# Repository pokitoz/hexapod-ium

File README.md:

# hexapod-ium

An hexapod robot using arduino and servo motors.
Manufacturing (PCB, 3D prints) and component assembly (PCBA) were done with PCBWay: https://www.pcbway.com/.

## Hardware

See the Kicad project in hw/ folder.

There is a Kicad Pluggin (https://www.pcbway.com/blog/News/PCBWay_Plug_In_for_KiCad_3ea6219c.html)
, 
simplifying the order process with PCBWay as the Gerber and BOM are filled in.

The design is reviewed and manufactured rapidely; which was very useful for this project.

### PCB

Kicad was used for the PCB design to add 2xPCA9865 and an ESP32.

### 3D Parts 

3D Printed parts can be done using a Prusa or Bamboo or any other 3d printer like the first iteration. 
But it was simpler to use PCBWay and the quality was better than printing on my own. The parameter used were:
- Resin Standard white material (UTR 8360)
- SLA

Design check and delivery was fast.

### Components

- 6x Leg (3 of them must be mirrored)
- 6x Holder
- 12 servo motors: MG90S or SG90 Micro Servo with screws
- 1 Arduino Uno
- PCA9865 (https://learn.adafruit.com/16-channel-pwm-servo-driver?view=all)
- Blu-tack
- Jumper cables

Need 5V for the motors board. VCC will be propagated to the main board (Arduino, ESP32,..)

You will need at least 2A upper limit to move all the motors at once.

## Software

### Arduino

Basic Arduino program to activate all the servo.
See the pinout in the .ino file. The VCC going out of the PCA9868 should go to the 5V of the board.

### ESP32

Might need driver https://www.silabs.com/developer-tools/usb-to-uart-bridge-vcp-drivers?tab=downloads

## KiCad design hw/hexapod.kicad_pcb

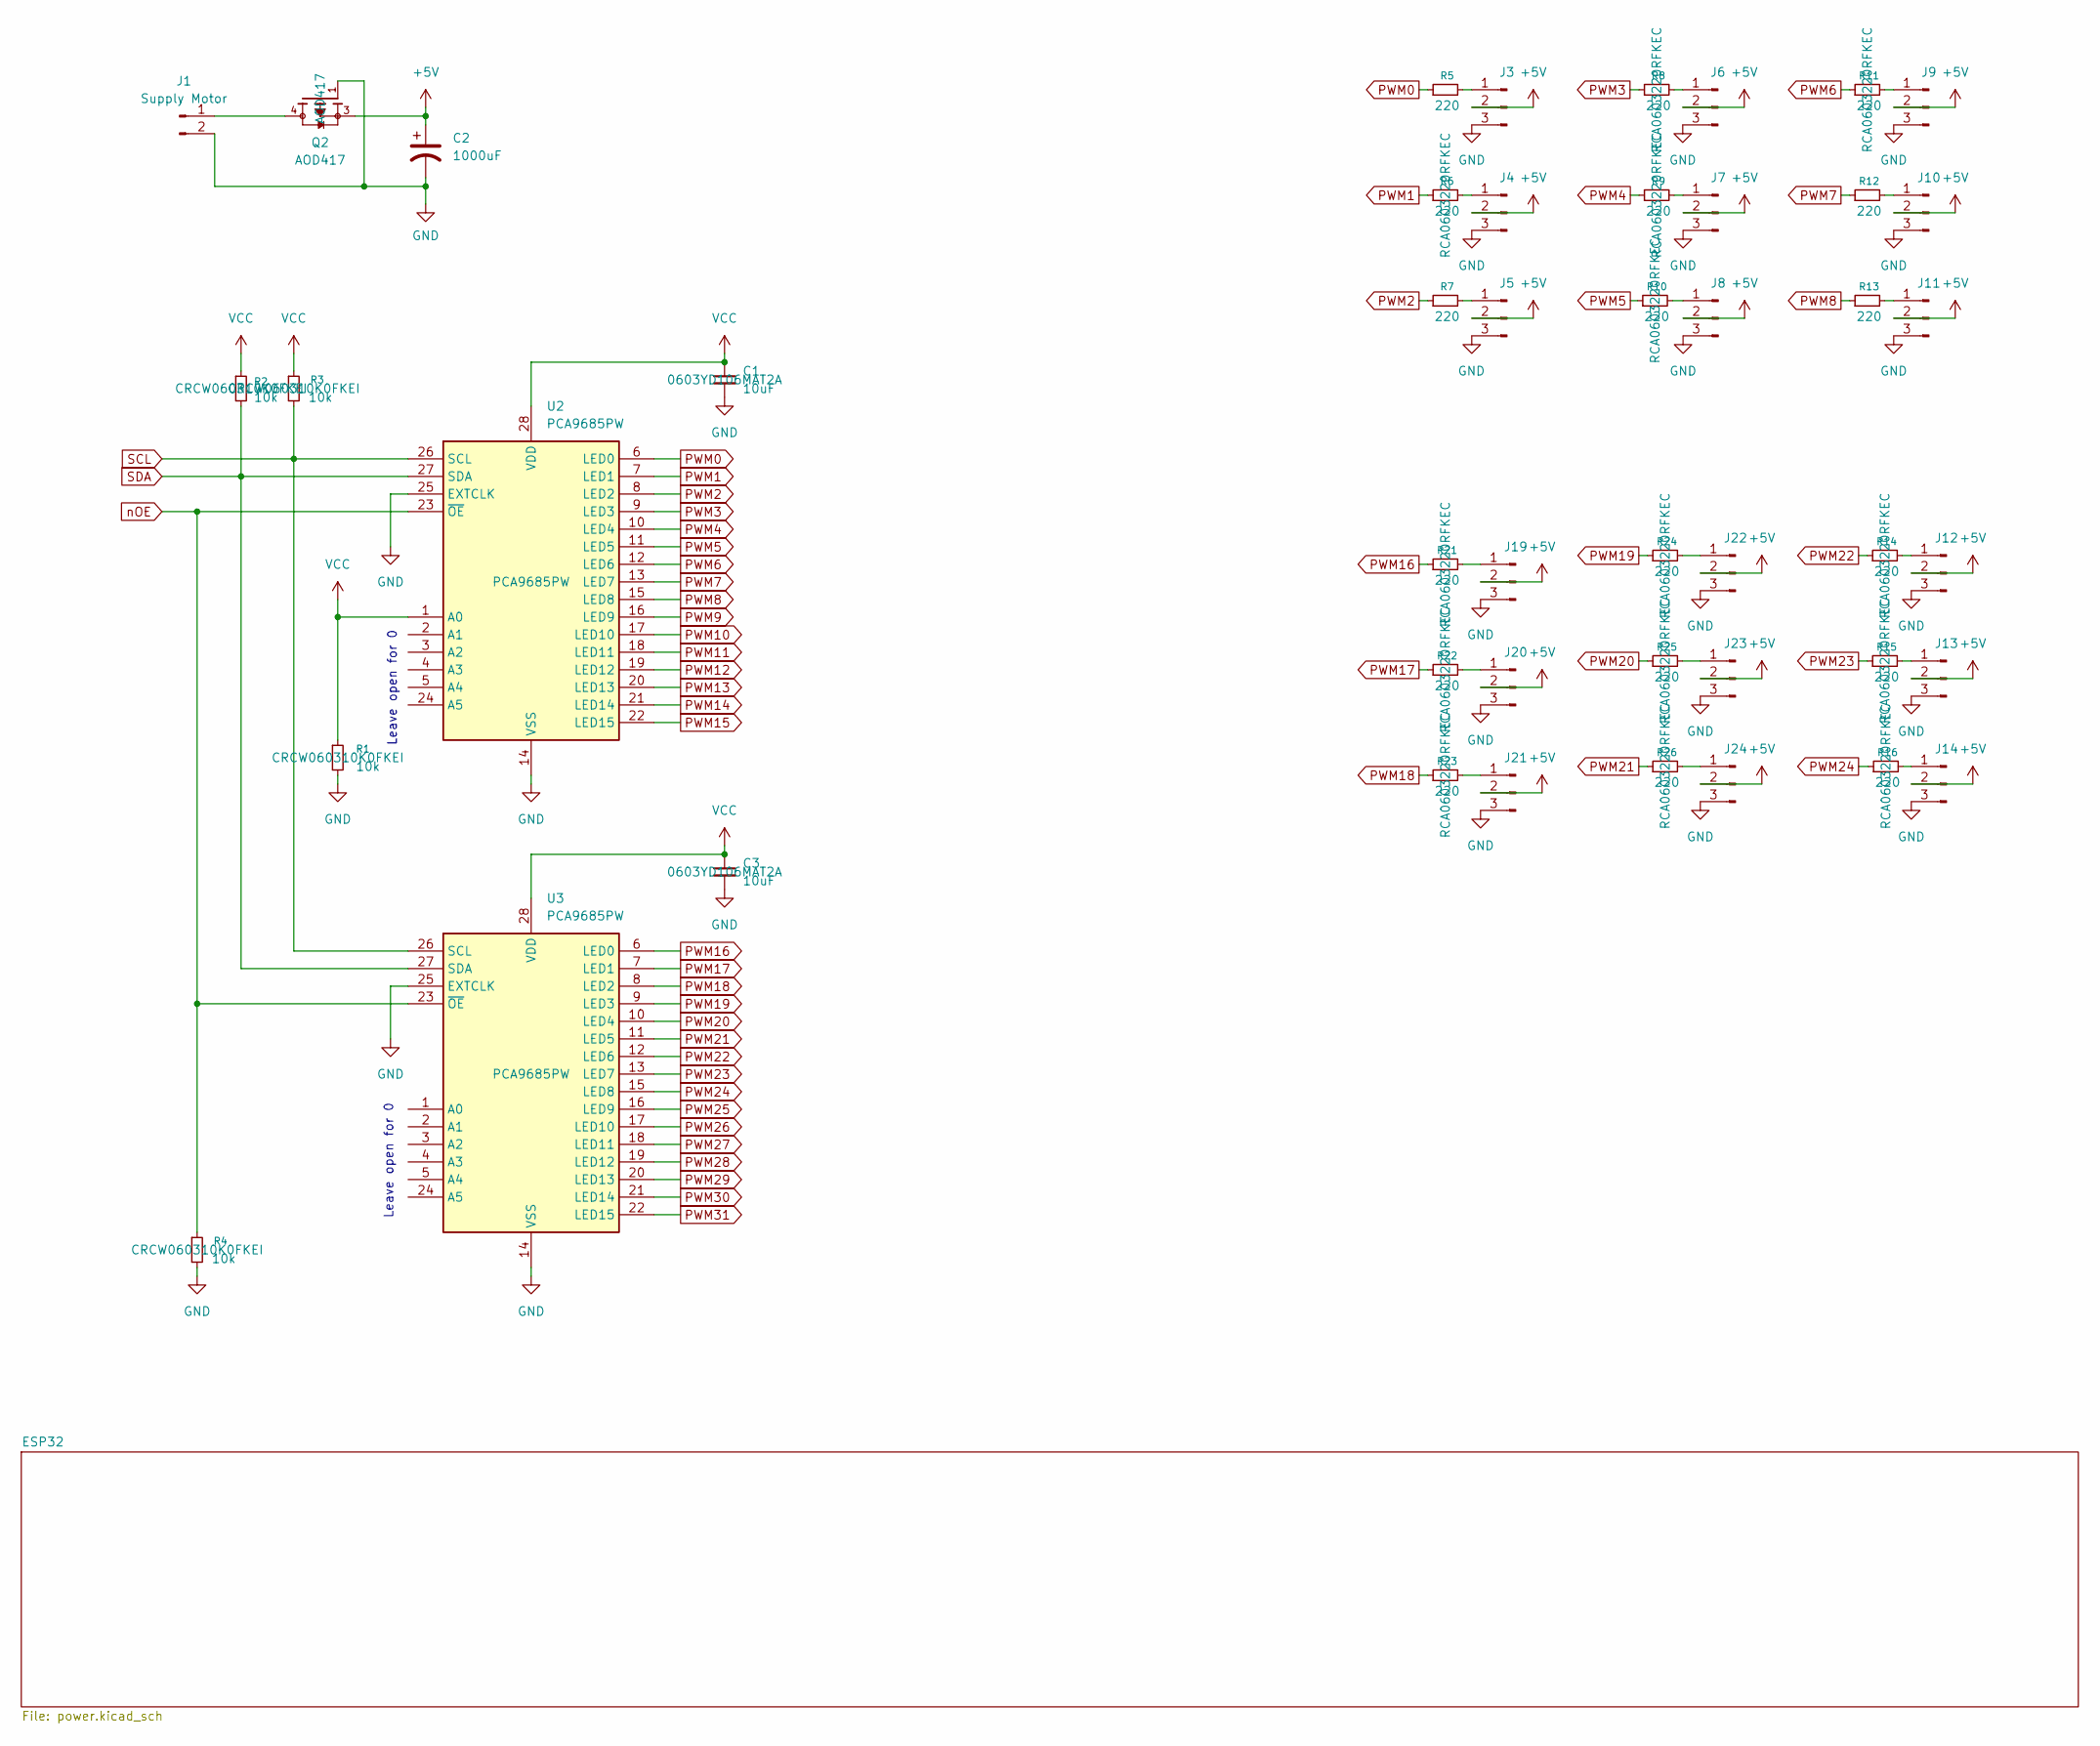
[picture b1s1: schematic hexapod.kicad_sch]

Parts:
C1, C3: 10uF; C_0603_1608Metric; Part 0603YD106MAT2A
C2: 1000uF; CAPPRD500W60D1000H1350
J1: Supply Motor; AMASS_XT30U-M_1x02_P5.0mm_Vertical
J3, J4, J5, J6, J7, J8, J9, J10, J11, J12, J13, J14, J19, J20, J21, J22, J23, J24: Conn_01x03_Pin; PinHeader_1x03_P2.54mm_Vertical
Q2: AOD417; DPAK228P994X240_3N; PARTREV U
R1, R2, R3, R4: 10k; R_0603_1608Metric_Pad0.98x0.95mm_HandSolder; Part CRCW060310K0FKEI
R5, R6, R7, R8, R9, R10, R11, R12, R13, R14, R15, R16, R21, R22, R23, R24, R25, R26: 220; R_0603_1608Metric_Pad0.98x0.95mm_HandSolder; Part RCA0603220RFKEC
U2, U3: PCA9685PW; TSSOP-28_4.4x9.7mm_P0.65mm; Part PCA9685PW

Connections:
+5V: C2.1, J3.2, J4.2, J5.2, J6.2, J7.2, J8.2, J9.2, J10.2, J11.2, J12.2, J13.2, J14.2, J19.2, J20.2, J21.2, J22.2, J23.2, J24.2, Q2.3
GND: C1.2, C2.2, C3.2, J1.2, J3.3, J4.3, J5.3, J6.3, J7.3, J8.3, J9.3, J10.3, J11.3, J12.3, J13.3, J14.3, J19.3, J20.3, J21.3, J22.3, J23.3, J24.3, Q2.1, R1.2, R4.2, U2.14 (VSS), U2.25 (EXTCLK), U3.14 (VSS), U3.25 (EXTCLK); also elsewhere on the board
unnamed: J1.1, Q2.4
unnamed: J3.1, R5.2
unnamed: J4.1, R6.2
unnamed: J5.1, R7.2
unnamed: J6.1, R8.2
unnamed: J7.1, R9.2
unnamed: J8.1, R10.2
unnamed: J9.1, R11.2
unnamed: J10.1, R12.2
unnamed: J11.1, R13.2
unnamed: J12.1, R14.2
unnamed: J13.1, R15.2
unnamed: J14.1, R16.2
unnamed: J19.1, R21.2
unnamed: J20.1, R22.2
unnamed: J21.1, R23.2
unnamed: J22.1, R24.2
unnamed: J23.1, R25.2
unnamed: J24.1, R26.2
PWM0: R5.1, U2.6 (LED0)
PWM1: R6.1, U2.7 (LED1)
PWM2: R7.1, U2.8 (LED2)
PWM3: R8.1, U2.9 (LED3)
PWM4: R9.1, U2.10 (LED4)
PWM5: R10.1, U2.11 (LED5)
PWM6: R11.1, U2.12 (LED6)
PWM7: R12.1, U2.13 (LED7)
PWM8: R13.1, U2.15 (LED8)
PWM9: U2.16 (LED9)
PWM10: U2.17 (LED10)
PWM11: U2.18 (LED11)
PWM12: U2.19 (LED12)
PWM13: U2.20 (LED13)
PWM14: U2.21 (LED14)
PWM15: U2.22 (LED15)
PWM16: R21.1, U3.6 (LED0)
PWM17: R22.1, U3.7 (LED1)
PWM18: R23.1, U3.8 (LED2)
PWM19: R24.1, U3.9 (LED3)
PWM20: R25.1, U3.10 (LED4)
PWM21: R26.1, U3.11 (LED5)
PWM22: R14.1, U3.12 (LED6)
PWM23: R15.1, U3.13 (LED7)
PWM24: R16.1, U3.15 (LED8)
PWM25: U3.16 (LED9)
PWM26: U3.17 (LED10)
PWM27: U3.18 (LED11)
PWM28: U3.19 (LED12)
PWM29: U3.20 (LED13)
PWM30: U3.21 (LED14)
PWM31: U3.22 (LED15)
SCL: R3.2, U2.26 (SCL), U3.26 (SCL); also elsewhere on the board
SDA: R2.2, U2.27 (SDA), U3.27 (SDA); also elsewhere on the board
VCC: C1.1, C3.1, R1.1, R2.1, R3.1, U2.1 (A0), U2.28 (VDD), U3.28 (VDD); also elsewhere on the board
nOE: R4.1, U2.23 (~OE), U3.23 (~OE)

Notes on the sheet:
Leave open for 0

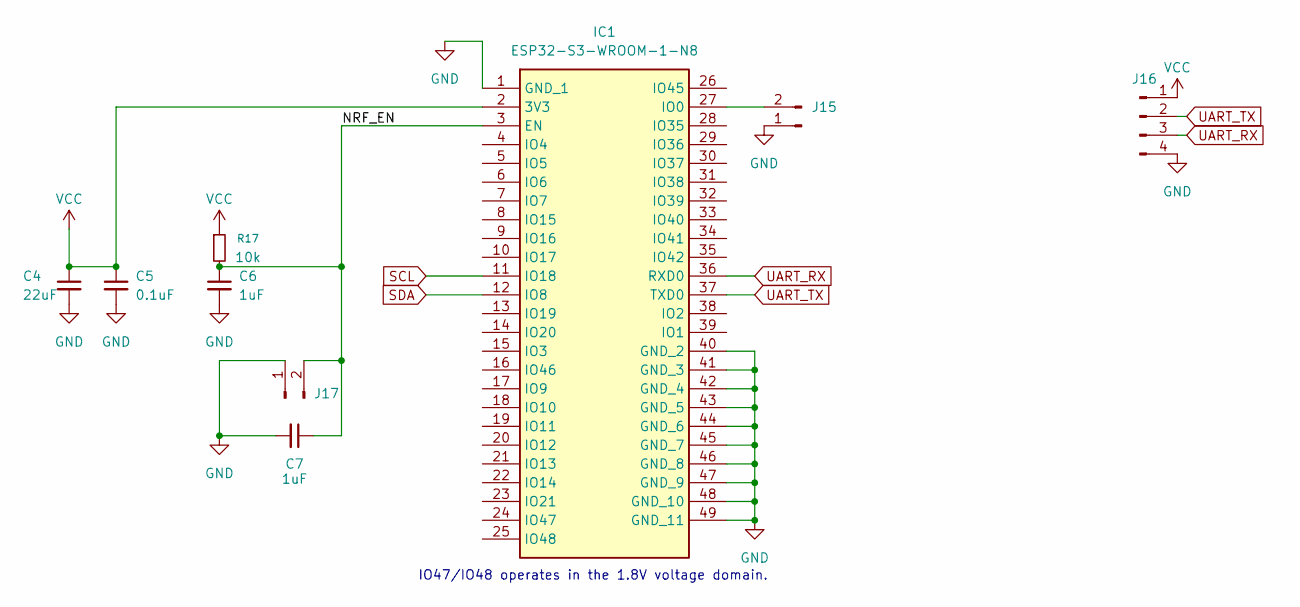
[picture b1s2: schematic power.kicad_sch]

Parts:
C4: 22uF; C_0603_1608Metric; Part 0603YD106MAT2A
C5: 0.1uF; C_0603_1608Metric; Part 0603YD106MAT2A
C6, C7: 1uF; C_0603_1608Metric; Part 0603YD106MAT2A
IC1: ESP32-S3-WROOM-1-N8; ESP32S3WROOM1N8R2; Mouser Part Number 356-ESP32-S3WROOM1N8
J15, J17: Conn_01x02_Pin; PinHeader_1x02_P2.54mm_Vertical
J16: Conn_01x04_Pin; PinHeader_1x04_P2.54mm_Vertical
R17: 10k; R_0603_1608Metric_Pad0.98x0.95mm_HandSolder; Part CRCW060310K0FKEI

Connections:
/ESP32/NRF_EN: C6.1, C7.1, IC1.3 (EN), J17.2, R17.2
GND: C4.2, C5.2, C6.2, C7.2, IC1.1 (GND_1), IC1.40 (GND_2), IC1.41 (GND_3), IC1.42 (GND_4), IC1.43 (GND_5), IC1.44 (GND_6), IC1.45 (GND_7), IC1.46 (GND_8), IC1.47 (GND_9), IC1.48 (GND_10), IC1.49 (GND_11), J15.1, J16.4, J17.1; also elsewhere on the board
unnamed: IC1.27 (IO0), J15.2
SCL: IC1.11 (IO18); also elsewhere on the board
SDA: IC1.12 (IO8); also elsewhere on the board
UART_RX: IC1.36 (RXD0), J16.3
UART_TX: IC1.37 (TXD0), J16.2
VCC: C4.1, C5.1, IC1.2 (3V3), J16.1, R17.1; also elsewhere on the board

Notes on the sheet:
IO47/IO48 operates in the 1.8V voltage domain.

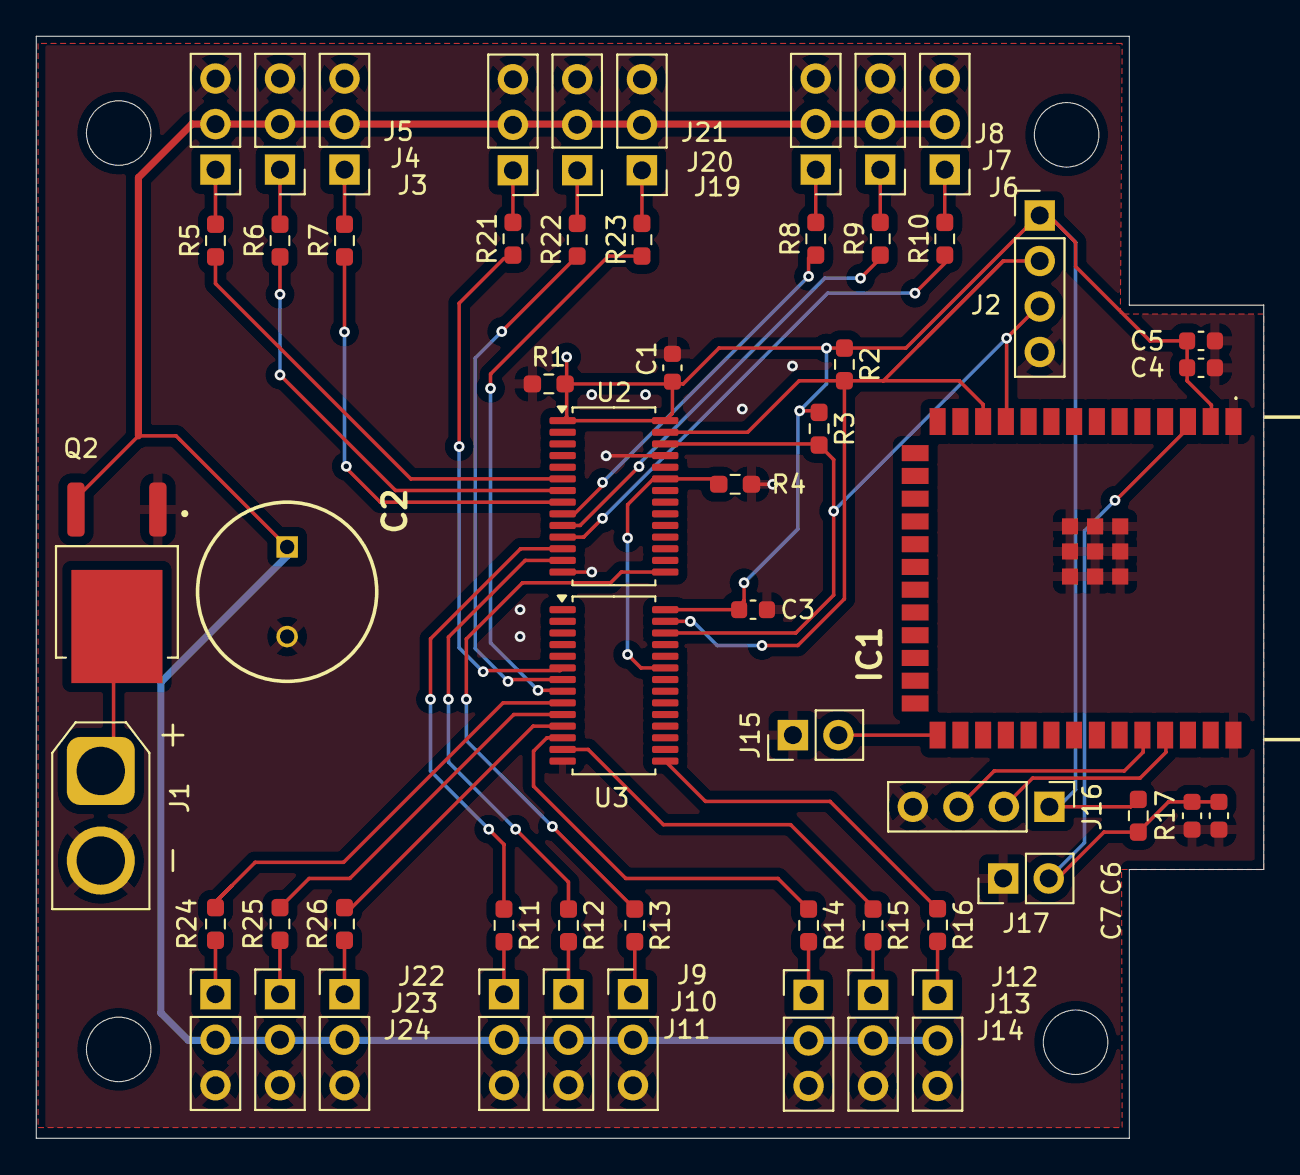
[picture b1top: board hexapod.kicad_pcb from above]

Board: 2 copper layers, 68.5 x 61.5 mm, 57 parts (0 on the bottom side), 47 nets.

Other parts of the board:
J2: Conn_01x04_Pin; PinHeader_1x04_P2.54mm_Vertical

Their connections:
GND: J2.4; also elsewhere on the board
SCL: J2.3; also elsewhere on the board
SDA: J2.2; also elsewhere on the board
VCC: J2.1; also elsewhere on the board

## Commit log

2022-09-17 Add 3d Print files
2022-09-17 Add ugly but working arduino code
2022-09-17 Add readme with picture
2025-04-12 Add ESP build
2025-04-12 Refactor esp32 code
2025-05-11 Add picture ESP32
2025-05-13 Add 3d picture
2025-05-13 Update STL
2025-05-15 Add HW files for motor pwm
2025-05-15 hw: Keep only needed pwm
2025-05-16 hw: Add ESP32
2025-05-25 Add MG90S
2025-07-26 readme: Add HW info
2025-07-26 readme: Add Picture
2025-07-26 readme: add link to kicad plugin for PCBWay
2025-07-26 readme: Add picture from PCBWay manufacturing
2025-08-06 Add more details about PCBWay order
